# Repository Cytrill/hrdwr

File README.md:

# hrdwr
Hardware (Case, PCB, Parts)

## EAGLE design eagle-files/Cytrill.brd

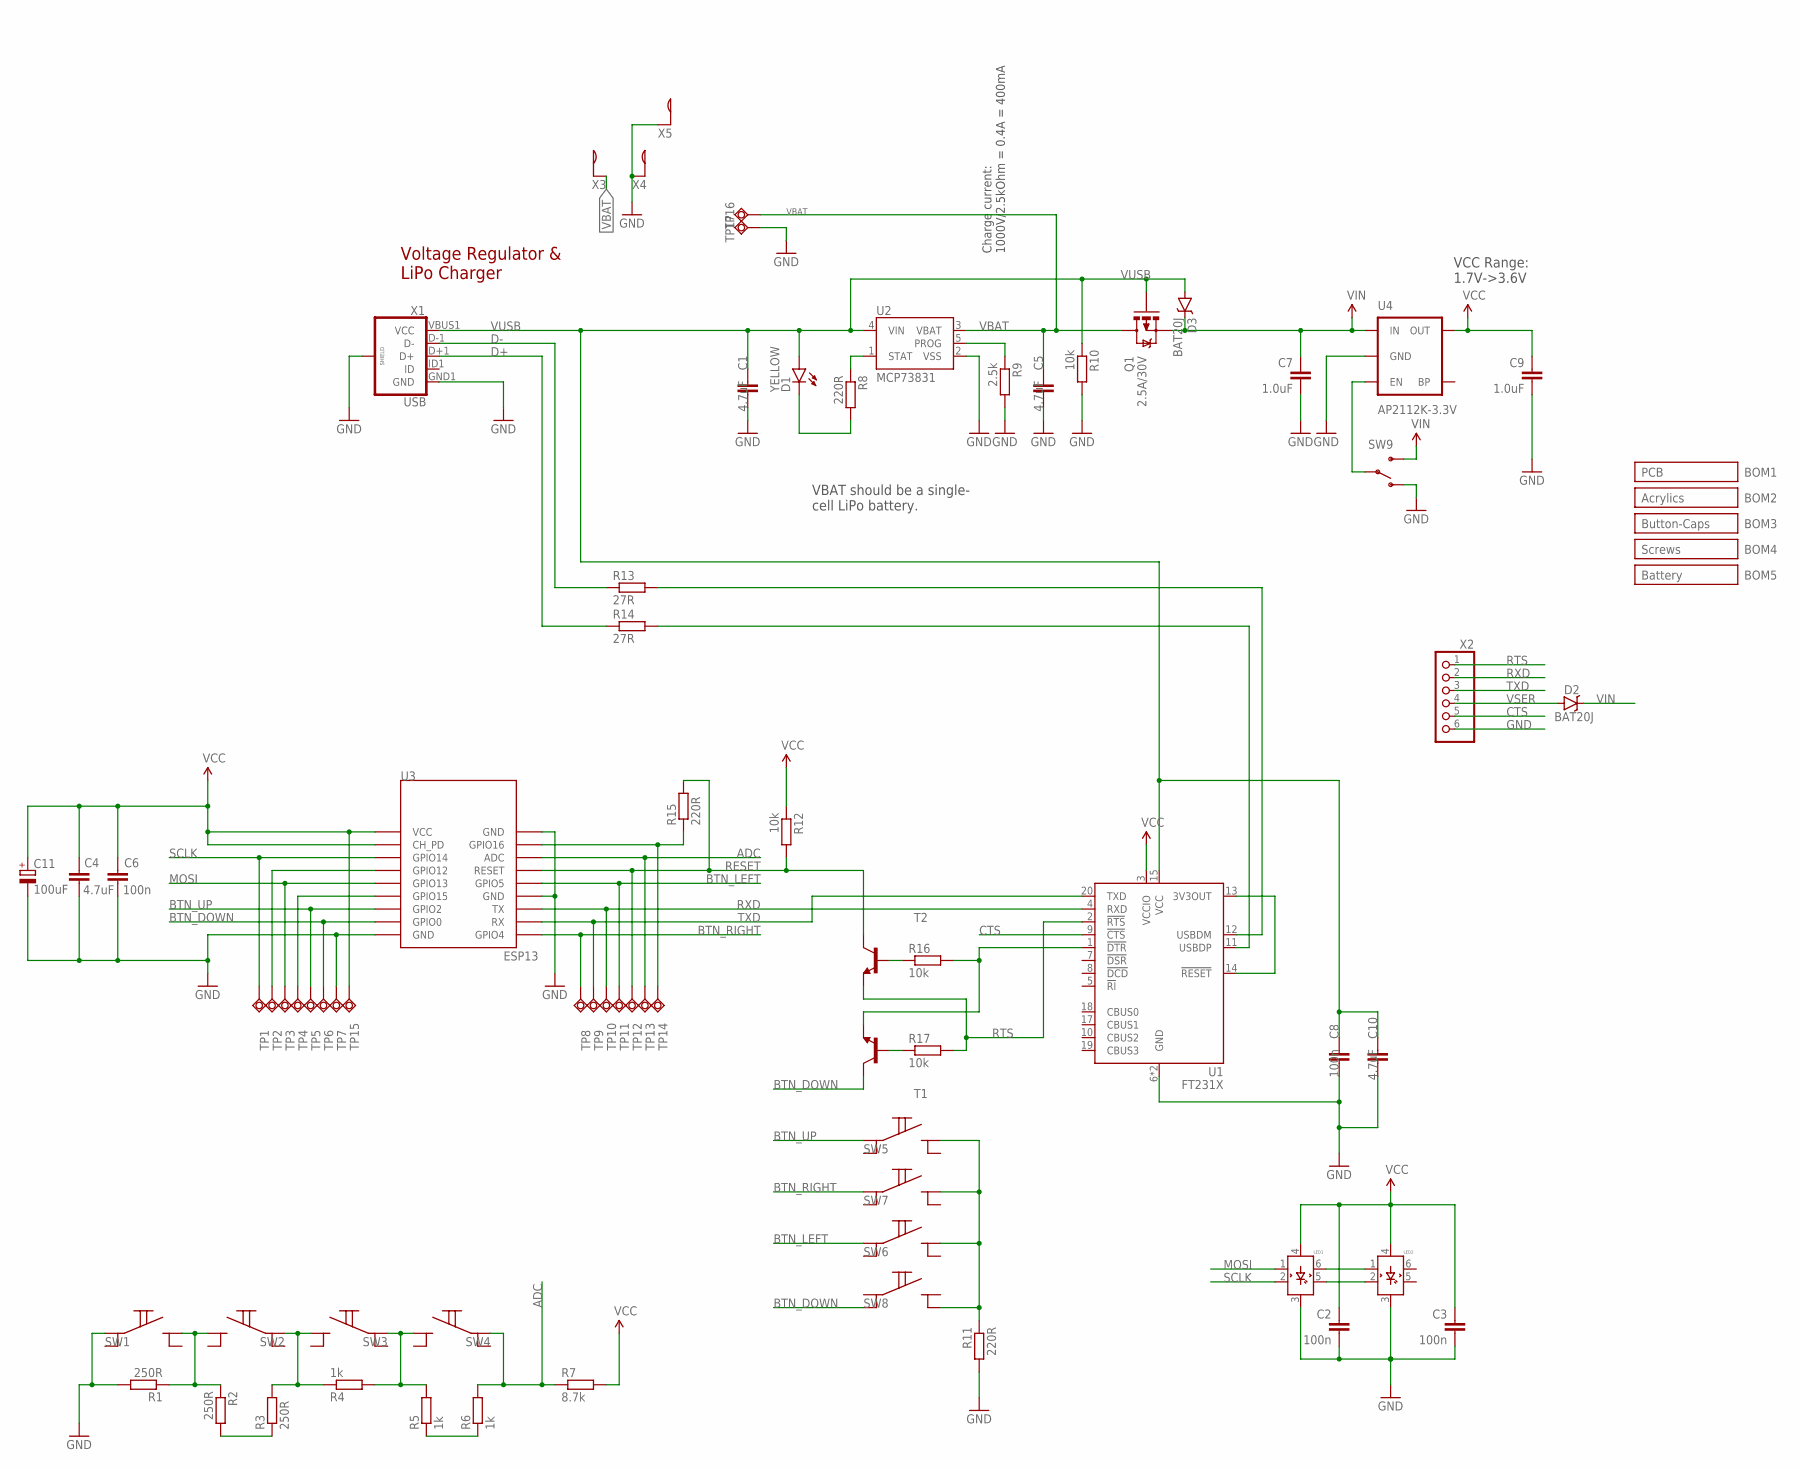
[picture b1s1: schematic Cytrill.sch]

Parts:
C1, C4, C5, C10: 4.7uF; C0603; PARTNO GRM188R61A475KE15D-MO
C2, C3, C6, C8: 100n; C0603; PARTNO C0603C104K4RACTU-MO
C7, C9: 1.0uF; C0603; PARTNO GRM188R61E105KA12D-MO
C11: 100uF; 3216-A; PARTNO TANTAL100UF
D1: YELLOW; LED-0603; PARTNO LYQ396P1Q236-MO
D2, D3: BAT20J; SOD-323; PARTNO BAT20JFILM-MO
LED1, LED2: APA102; RGBLED5050; PARTNO APA102
Q1: 2.5A/30V; SOT23-3; PARTNO DMP3130L-7-MO
R1, R2, R3: 250R; R0603; PARTNO ERJ3EKF2490V-MO
R4, R5, R6: 1k; R0603; PARTNO ERJ3EKF1001V-MO
R7: 8.7k; R0603; PARTNO ERJ3EKF8661V-MO
R8, R11, R15: 220R; R0603; PARTNO ERJ3EKF2200V-MO
R9: 2.5k; R0603; PARTNO ERJ3EKF2491V-MO
R10, R12, R16, R17: 10k; R0603; PARTNO ERJ3EKF1002V-MO
R13, R14: 27R; R0603; PARTNO ERJ3EKF27R0V-MO
SW1, SW2, SW3, SW4, SW5, SW6, SW7, SW8: TACTSWITCH6MM; TACTSWITCH; PARTNO 101-0364-EV-MO
SW9: SWITCH-SPDT-SMD-A; SWITCH-SPST-SMD-A; PARTNO SSSS810701
T1, T2: BC847C-NPN-SOT23-BEC; SOT23-BEC; PARTNO BC847C-MO
TP1, TP2, TP3, TP4, TP5, TP6, TP7, TP8, TP9, TP10, TP11, TP12, TP13, TP14, TP15: TPSQTP15SQ; TP15SQ; PARTNO TESTPAD
TP16, TP17: TPSQTP20R; TP20R; PARTNO TESTPAD
U1: FT231X; SSOP20; PARTNO FT231XS
U2: MCP73831; SOT23-5; PARTNO MCP73831T-2ATI/OT
U3: ESP13; PARTNO esp-13
U4: AP2112K-3.3V; SOT23-5; PARTNO AP2112K-3.3
X1: USB; USB-B-MICRO-SMD_V03
X2: PINHD-1X6/90-SMD; 1X06/90-SMD; PARTNO 961106-5500-AR-PR-MO
X3, X4, X5: BATTERYTERMINAL; KEYSTONE-55; PARTNO KS55-MO

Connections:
ADC: R6.2, R7.1, SW4.A@1 (A), TP13.TP, U3.ADC
BTN_DOWN: SW8.A@2 (A1), T1.3 (C), TP6.TP, U3.GPIO0
BTN_LEFT: SW6.A@1 (A), TP11.TP, U3.GPIO5
BTN_RIGHT: SW7.A@1 (A), TP8.TP, U3.GPIO4
BTN_UP: SW5.A@1 (A), TP5.TP, U3.GPIO2
CTS: U1.9 (!CTS), X2.5
D+: R14.1, X1.D+1 (D+)
D-: R13.1, X1.D-1 (D-)
GND: C1.2, C2.2, C3.2, C4.2, C5.2, C6.2, C7.2, C8.2, C9.2, C10.2, C11.-, LED1.3 (GND), LED2.3 (GND), R1.2, R9.2, R10.2, R11.2, SW1.A@1 (A), SW9.1 (O), TP7.TP, TP17.TP, U1.6 (GND), U1.16 (GND), U2.2 (VSS), U3.GND@0 (GND), U3.GND@1 (GND), U3.GND@2 (GND), U4.2 (GND), X1.GND1 (GND), X1.SHIELD1 (SHIELD), X1.SHIELD2 (SHIELD), X2.6, X4.1@1, X4.1@2, X5.1@1, X5.1@2
MOSI: LED1.1 (DIN), TP3.TP, U3.GPIO13
unnamed: LED1.6 (DOUT), LED2.1 (DIN)
unnamed: LED1.5 (COUT), LED2.2 (CIN)
unnamed: R11.1, SW5.B@1 (B), SW6.B@1 (B), SW7.B@1 (B), SW8.B@2 (B1)
unnamed: R14.2, U1.11 (USBDP)
unnamed: R15.1, TP14.TP, U3.GPIO16
unnamed: R1.1, R2.1, SW1.B@1 (B), SW2.B@1 (B)
unnamed: R3.2, R4.1, SW2.A@1 (A), SW3.B@1 (B)
unnamed: R4.2, R5.2, SW3.A@1 (A), SW4.B@1 (B)
unnamed: R13.2, U1.12 (USBDM)
unnamed: U1.13 (3V3OUT), U1.14 (!RESET)
unnamed: SW9.2, U4.3 (EN)
unnamed: R16.1, T2.1 (B)
unnamed: R5.1, R6.1
unnamed: R9.1, U2.5 (PROG)
unnamed: R2.2, R3.1
unnamed: TP2.TP, U3.GPIO12
unnamed: D1.C, R8.2
unnamed: R8.1, U2.1 (STAT)
unnamed: TP4.TP, U3.GPIO15
unnamed: R17.1, T1.1 (B)
unnamed: R16.2, T1.2 (E), U1.1 (!DTR)
RESET: R12.2, R15.2, T2.3 (C), TP12.TP, U3.RST (RESET)
RTS: R17.2, T2.2 (E), U1.2 (!RTS), X2.1
RXD: TP10.TP, U1.4 (RXD), U3.TXD (TX), X2.2
SCLK: LED1.2 (CIN), TP1.TP, U3.GPIO14
TXD: TP9.TP, U1.20 (TXD), U3.RXD (RX), X2.3
VBAT: C5.1, Q1.3 (D), TP16.TP, U2.3 (VBAT), X3.1@1, X3.1@2
VCC: C2.1, C3.1, C4.1, C6.1, C9.1, C11.+, LED1.4 (VDD), LED2.4 (VDD), R7.2, R12.1, TP15.TP, U1.3 (VCCIO), U3.CH_PD, U3.VCC, U4.5 (OUT)
VIN: C7.1, D2.C, D3.C, Q1.2 (S), SW9.3 (S), U4.1 (IN)
VSER: D2.A, X2.4
VUSB: C1.1, C8.1, C10.1, D1.A, D3.A, Q1.1 (G), R10.1, U1.15 (VCC), U2.4 (VIN), X1.VBUS1 (VCC)

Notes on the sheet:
Voltage Regulator & LiPo Charger
VCC Range: 1.7V->3.6V
VBAT should be a single- cell LiPo battery.
Charge current: 1000V/2.5kOhm = 0.4A = 400mA

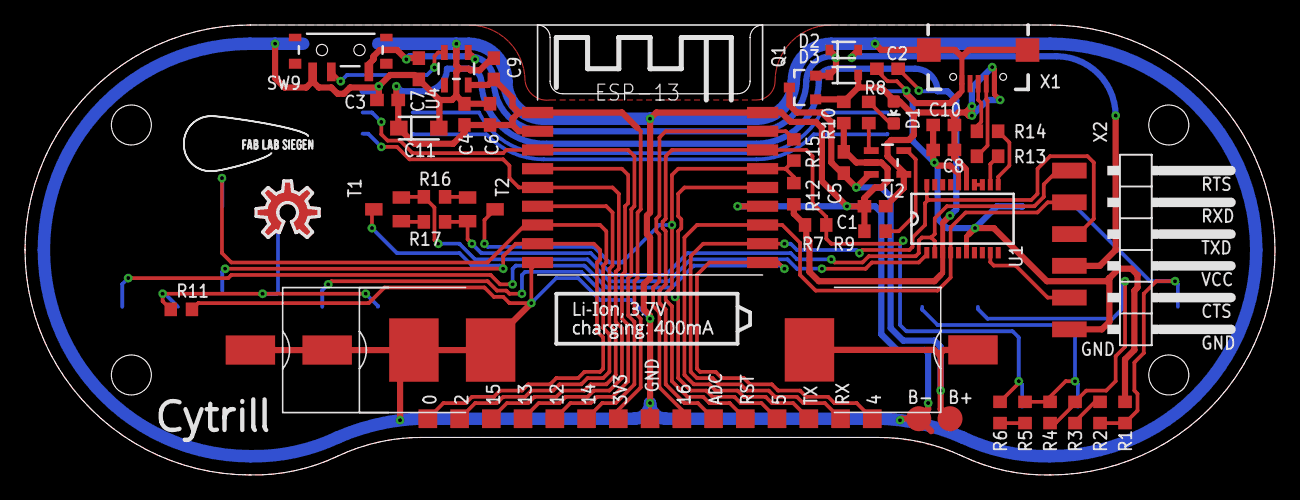
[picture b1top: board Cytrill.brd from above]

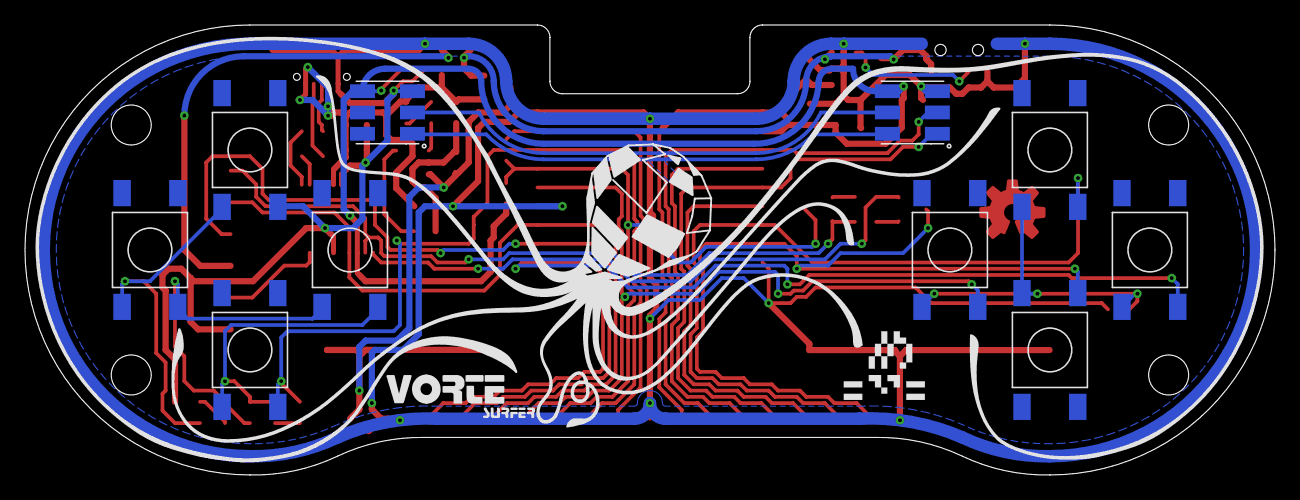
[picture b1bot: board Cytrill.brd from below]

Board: 2 copper layers, 100.0 x 36.0 mm, 77 parts (13 on the bottom side), 41 nets.

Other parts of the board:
U$1: FABLAB-KLEIN
U$2: SIMON-LOGO
U$3: HASII
U$4: VORTEX-KLEIN.1
U$5: OSHWLOGO_TOP_0.2
U$6: OCTO

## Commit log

2015-08-25 added blender 3d mockup
2016-03-09 3d printed case initial commit
2016-07-04 Eagle files for Cytrill. Slightly more refined compared to the 1st run of PCBs
